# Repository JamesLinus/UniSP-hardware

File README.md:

# UniSP-hardware
(..sketch..)

## About UniSP

UniSP is an open source project that aims to develop universal high power SMPS (Swiched-mode power supply) platform.

Main features:
- based on full bridge DC/DC converter
- digital controll based on STM32F334 microcontroller
- modular desing
- communication interface
- output module interface

Source code and doc for software part of project can be find on <https://github.com/UniSP/UniSP-software>

## About UniSP-hardware

UniSP-hardware is dividing into the following modules:
- **UniSP-mainboard** - main power section including primary and secondary side of converter.
- **UniSP-pfc-LT1249** - active power factor correction based on Linear LT1249.
- **UniSP-pfc-bl** - (planned) bridgeless PFC with low power supply on board.
- **UniSP-driver** - main control unit with STM32F334R8 uC on board
- **UniSP-bridge_driver** - full bridge transistors driver.
- **UniSP-bridge_driver_PSFB** - (planned) full bridge transistors driver supporting phase shifted resonant PWM controll technique.
- **UniSP-rectifier_driver** - (planned) synchronous rectifier transistors driver (GDT?).
- Optionally output module (**UniSP-out_module**) controled by UniSP output interface.

Each module (except UniSP output modules) is placed in individual subfolder in UniSP-hardware repository. 

UniSP output modules (hardware and software) will be places in a separated repositories.

UniSP output interface consists of:
- 2 current sense input (fast speed and normal speed)
- 2 voltage sense input (fast speed and normal speed)
- 2 high-resolution timer outputs (TIMERD and TIMERE - each with 2 channel)
- 15V supply output
  
### Details

| Module                  | Circuit diagram                                      | PCB status   | Next action         |
|-------------------------|------------------------------------------------------|--------------|---------------------|
| UniSP-mainboard         | [Link](doc/scheme/UniSP-mainboard.pdf)               | In progress  |                     |
| UniSP-pfc-LT1249        | [Link](doc/scheme/UniSP-pfc-LT1249.pdf)              | In progress  | Add aux PS section  |
| UniSP-pfc-bl            | In progress                                          | ----         |                     |
| UniSP-driver            | [Link](doc/scheme/UniSP-driver.pdf)                  | In progress  |                     |
| UniSP-bridge_driver     | [Link](doc/scheme/UniSP-bridge_driver.pdf)           | Done         |                     |
| UniSP-bridge_driver_PSFB| [Link](doc/scheme/UniSP-bridge_driver_PSFB.pdf)      | In progress  |                     |
| UniSP-rectifier_driver  | In progress                                          | ----         |                     |

Please visit the author's website ~~www.railab.me~~ (under construction) for worklogs, articles and other interesting content ;]

### TODO
- finish new mainboard PCB
- add 3D models
- add modules to official KiCad library
- 3D model (in FreeCAD)
- chassis
- EMI/RFI shielding ?
- improve EMC

### UniSP-hardware roadmap
- documentation
- costs optimisation
- user interface
- synchronous rectification on secondary side
- soft swiching on primary side (phase shifted full bridge)
- bridgeless PFC

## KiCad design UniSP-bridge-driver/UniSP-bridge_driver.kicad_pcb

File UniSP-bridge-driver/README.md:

#UniSP-bridge_driver-v.0.2

### Basic spec

### TODO in next revision
- SMT transformers?
- some testing pads?

### History
v0.1:

- Initial revision.

v0.2:

- Fixed some bug.
- Github init.

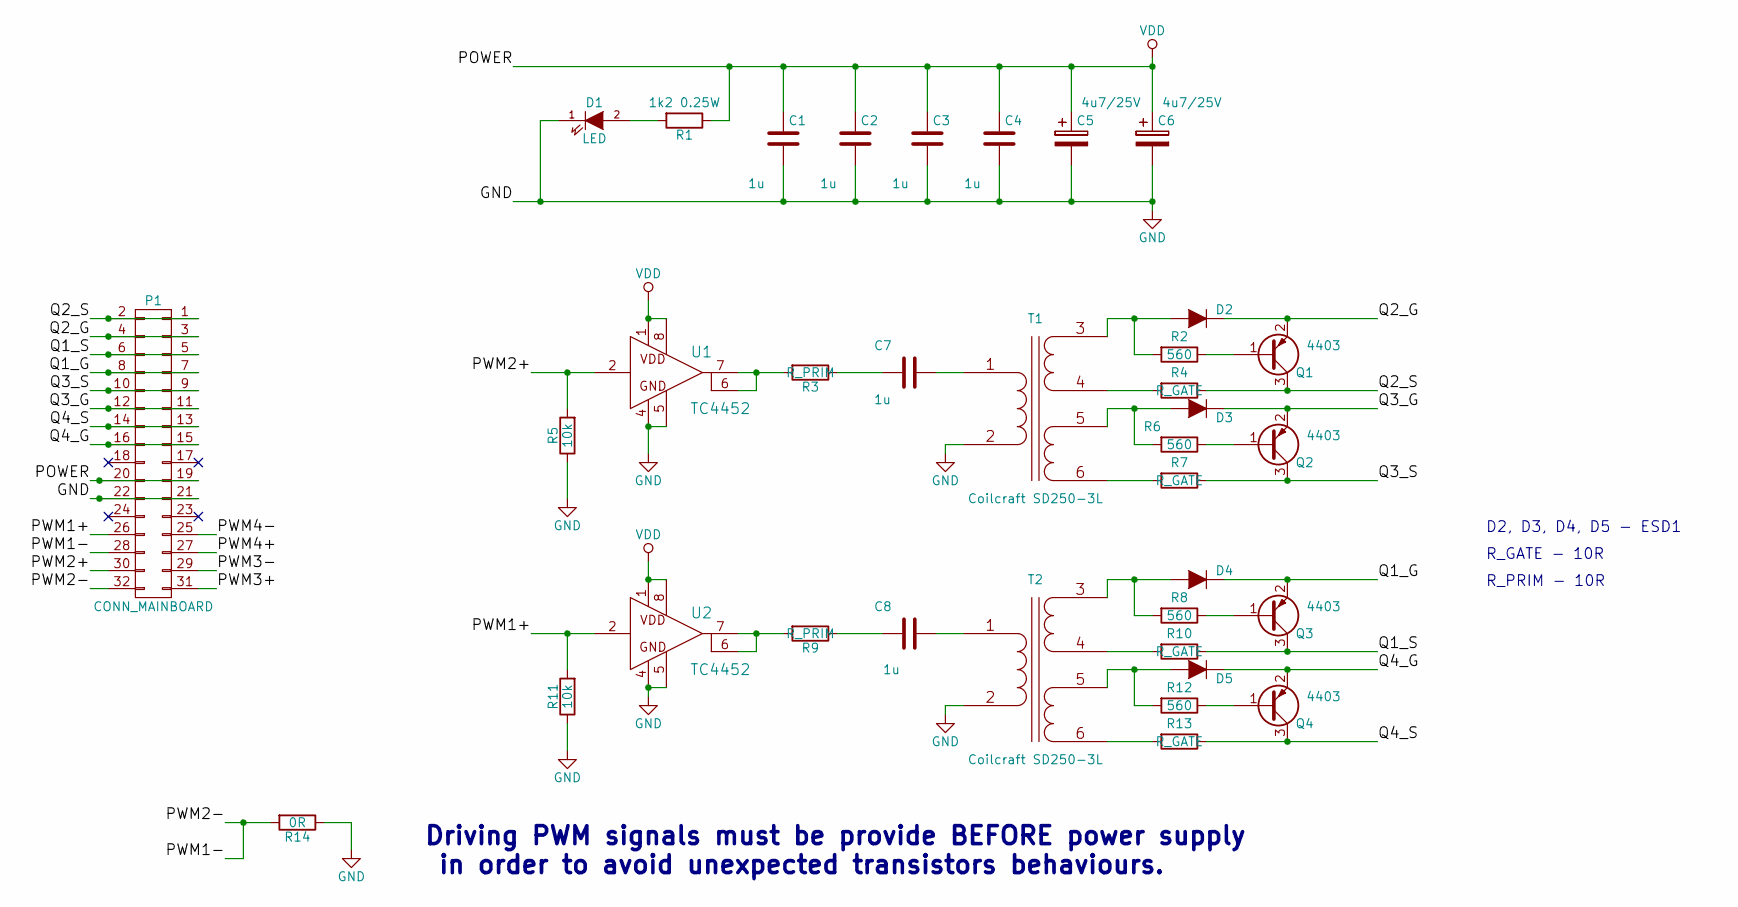
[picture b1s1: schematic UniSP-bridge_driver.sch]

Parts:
C1, C2, C3, C4, C7, C8: 1u; C_1206_HandSoldering
C5, C6: 4u7/25V; TantalC_SizeB_EIA-3528_HandSoldering
D1: LED; LED-0603
D2, D3, D4, D5: ESD1; SMA_Handsoldering
P1: CONN_MAINBOARD; Pin_Header_Angled_2x16
Q1, Q2, Q3, Q4: 4403; SOT-23_Handsoldering
R1: 1k2 0.25W; R_1206_HandSoldering
R2, R6, R8, R12: 560; R_1206_HandSoldering
R3, R9: R_PRIM; R_1206_HandSoldering
R4, R7, R10, R13: R_GATE; R_1206_HandSoldering
R5, R11: 10k; R_0805_HandSoldering
R14: 0R; R_0805_HandSoldering
T1, T2: Coilcraft SD250-3L; Coilcraft-SD250-3L
U1, U2: TC4452; SOIC-8_3.9x4.9mm_Pitch1.27mm

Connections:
/PWM1+: P1.26, R11.2, U2.2
/PWM1-: P1.28, P1.32, R14.2
/PWM2+: P1.30, R5.2, U1.2
/PWM3+: P1.31
/PWM3-: P1.29
/PWM4+: P1.27
/PWM4-: P1.25
/Q1_G: D4.1 (K), P1.7, P1.8, Q3.2 (E)
/Q1_S: P1.5, P1.6, Q3.3 (C), R10.1
/Q2_G: D2.1 (K), P1.3, P1.4, Q1.2 (E)
/Q2_S: P1.1, P1.2, Q1.3 (C), R4.1
/Q3_G: D3.1 (K), P1.11, P1.12, Q2.2 (E)
/Q3_S: P1.9, P1.10, Q2.3 (C), R7.1
/Q4_G: D5.1 (K), P1.15, P1.16, Q4.2 (E)
/Q4_S: P1.13, P1.14, Q4.3 (C), R13.1
GND: C1.2, C2.2, C3.2, C4.2, C5.2, C6.2, D1.1 (K), P1.21, P1.22, R5.1, R11.1, R14.1, T1.2 (AB), T2.2 (AB), U1.4, U1.5, U2.4, U2.5
unnamed: C7.1, T1.1 (AA)
unnamed: C7.2, R3.1
unnamed: C8.1, T2.1 (AA)
unnamed: C8.2, R9.1
unnamed: D1.2 (A), R1.2
unnamed: D2.2 (A), R2.2, T1.3 (SA)
unnamed: D3.2 (A), R6.2, T1.5 (SC)
unnamed: D4.2 (A), R8.2, T2.3 (SA)
unnamed: D5.2 (A), R12.2, T2.5 (SC)
unnamed: Q1.1 (B), R2.1
unnamed: Q2.1 (B), R6.1
unnamed: Q3.1 (B), R8.1
unnamed: Q4.1 (B), R12.1
unnamed: R3.2, U1.6, U1.7
unnamed: R4.2, T1.4 (SB)
unnamed: R7.2, T1.6 (SD)
unnamed: R9.2, U2.6, U2.7
unnamed: R10.2, T2.4 (SB)
unnamed: R13.2, T2.6 (SD)
VDD: C1.1, C2.1, C3.1, C4.1, C5.1, C6.1, P1.19, P1.20, R1.1, U1.1, U1.8, U2.1, U2.8

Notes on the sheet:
D2, D3, D4, D5 - ESD1
Driving PWM signals must be provide BEFORE power supply in order to avoid unexpected transistors behaviours.
R_GATE - 10R
R_PRIM - 10R

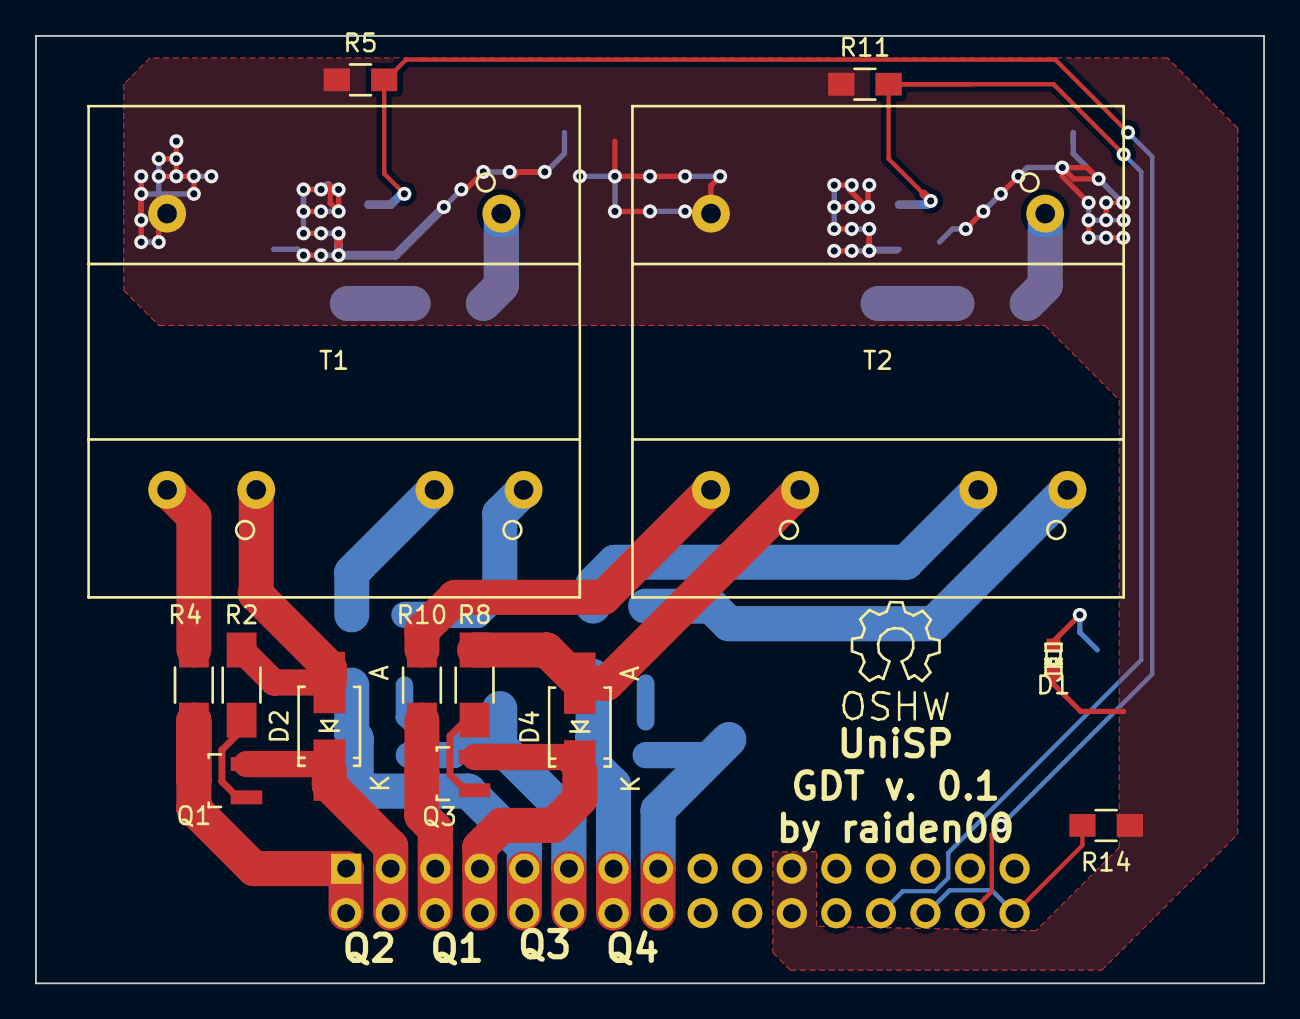
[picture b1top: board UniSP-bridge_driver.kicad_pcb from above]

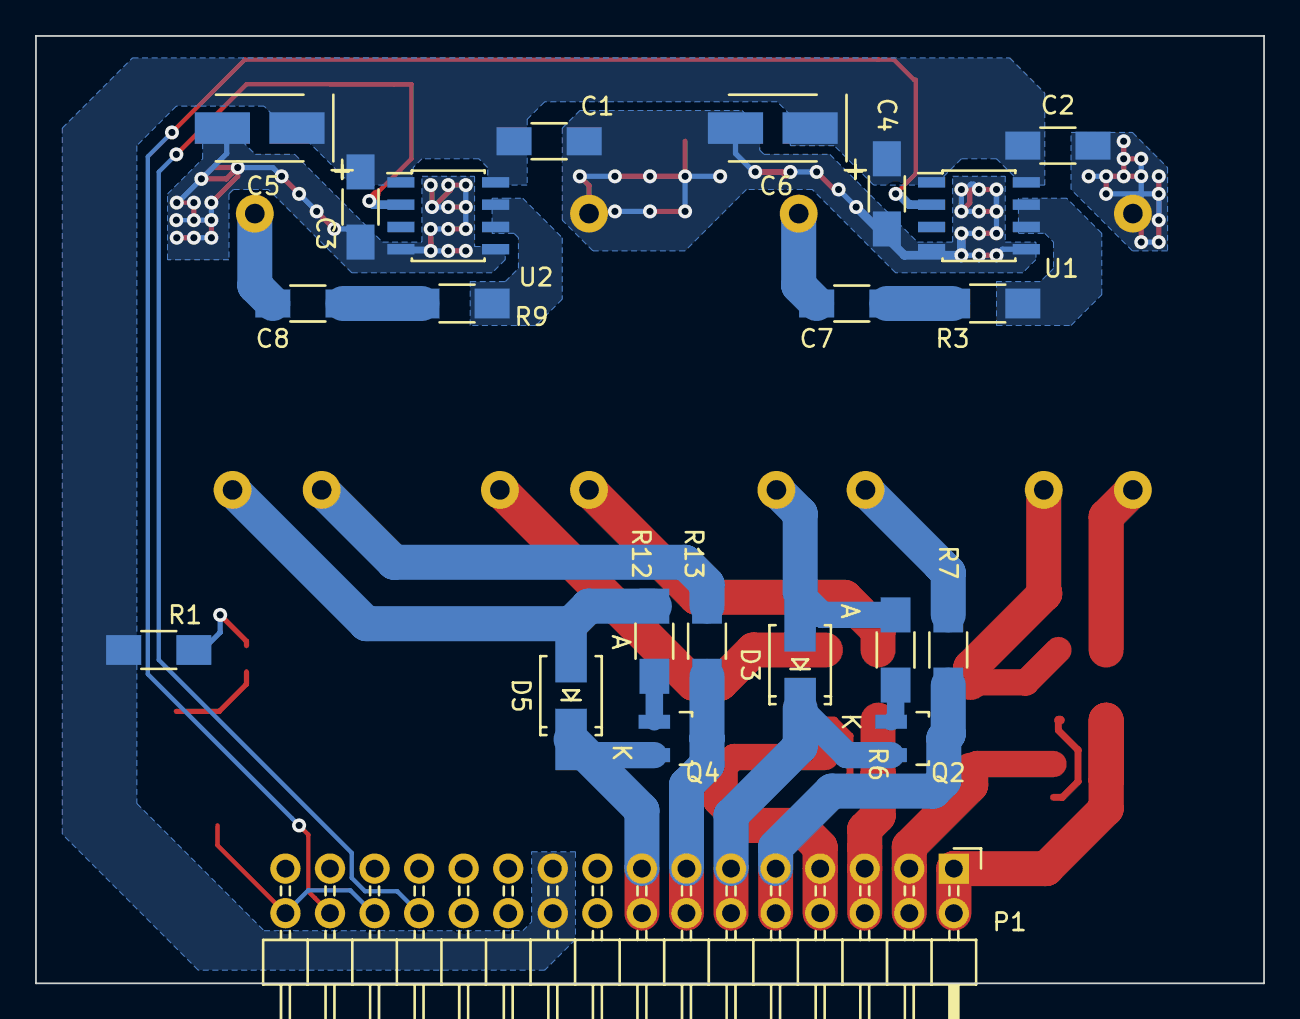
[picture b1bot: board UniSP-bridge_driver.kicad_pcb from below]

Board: 2 copper layers, 70.0 x 54.0 mm, 36 parts (22 on the bottom side), 32 nets.

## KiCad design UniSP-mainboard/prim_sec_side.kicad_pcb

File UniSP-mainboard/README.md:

# UniSP-mainboard-v.0.2

### Basic spec

### TODO
- finish PCB
- test points?

### History
v0.1:

- Initial revision.

v0.2:

- Fixed some bug.
- Added optional inductance in series with transformer.
- CT now ahed of transistors bridge.
- Github init.

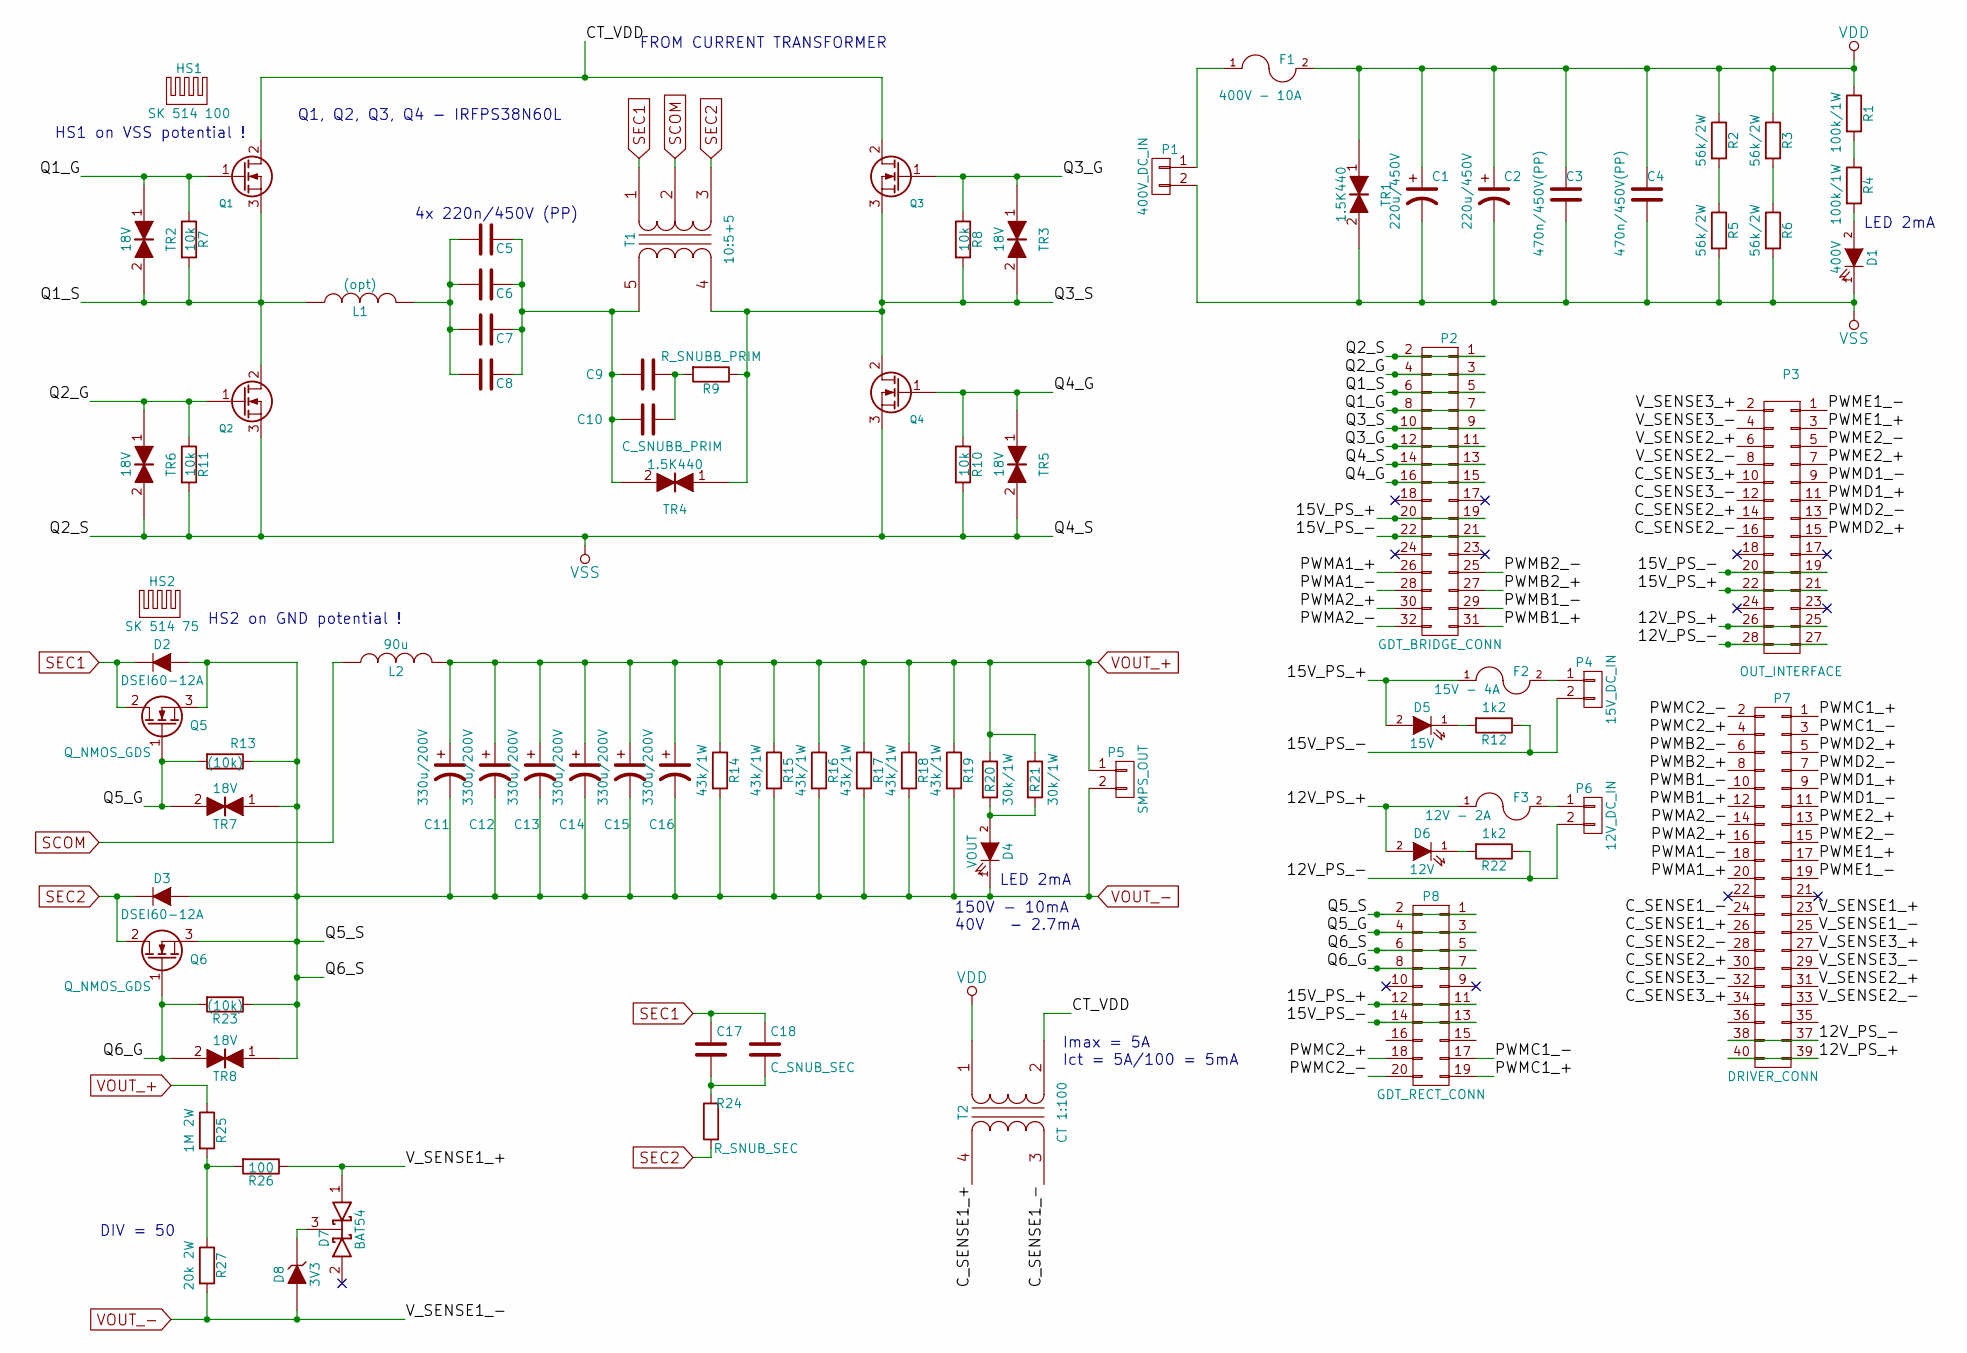
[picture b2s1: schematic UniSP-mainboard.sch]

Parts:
C1, C2: 220u/450V; C_Radial_D30_L51_P10
C3, C4: 470n/450V(PP); C_Rect_L32_W15_P27
C5, C6, C7, C8: 220n/450V (PP); C_Rect_L18_W9_H15_P15
C9, C10: C_SNUBB_PRIM; C_Rect_L7_W6_P5
C11, C12, C13, C14, C15, C16: 330u/200V; C_Radial_D22_L41_P10
C17, C18: C_SNUB_SEC; C_Rect_L7_W6_P5
D1: 400V; LED-3MM
D2, D3: DSEI60-12A; Diode_TO-247_Vertical
D4: VOUT; LED-3MM
D5: 15V; LED-0603
D6: 12V; LED-0603
D7: BAT54; SOT-23_Handsoldering
D8: 3V3; MiniMELF_Handsoldering
F1: 400V - 10A; FUSE_3
F2: 15V - 4A; Smps-fuse-154
F3: 12V - 2A; Smps-fuse-154
HS1: SK 514 100; Heatsink-SK-514-100
HS2: SK 514 75; Heatsink-SK-514-75
L1: (opt); Inductor-DTMSS40-0.1-20
L2: 90u; Inductor-DTMSS40-0.1-20
P1: 400V_DC_IN; CONN_2_20A
P2: GDT_BRIDGE_CONN; Socket_Strip_Straight_2x16
P3: OUT_INTERFACE; Socket_Strip_Straight_2x14
P4: 15V_DC_IN; bornier2
P5: SMPS_OUT; CONN_2_20A
P6: 12V_DC_IN; bornier2
P7: DRIVER_CONN; Socket_Strip_Straight_2x20
P8: GDT_RECT_CONN; Socket_Strip_Straight_2x10
Q1, Q2, Q3, Q4: IRFPS38N60L; TO-247_Vertical_Neutral123_largePads
Q5, Q6: Q_NMOS_GDS; TO-247_Vertical_Neutral123_largePads
R1, R4: 100k/1W; R_2512_HandSoldering
R2, R3, R5, R6: 56k/2W; R_2512_HandSoldering
R7, R8, R10, R11: 10k; R_2512_HandSoldering
R9: R_SNUBB_PRIM; Resistor_Vertical_RM7.5mm
R12, R22: 1k2; R_1206_HandSoldering
R13, R23: (10k); R_2512_HandSoldering
R14, R15, R16, R17, R18, R19: 43k/1W; R_2512_HandSoldering
R20, R21: 30k/1W; R_2512_HandSoldering
R24: R_SNUB_SEC; Resistor_Vertical_RM7.5mm
R25: 1M 2W; Resistor_Horizontal_RM15mm
R26: 100; R_1206_HandSoldering
R27: 20k 2W; Resistor_Horizontal_RM15mm
T1: 10:5+5; TRAFO2_E71_H
T2: CT 1:100; Coilcraft-CS1xxx
TR1, TR4: 1.5K440; Diode-DO-214AB_Handsoldering
TR2, TR3, TR6, TR7, TR8: 18V; SMB_Handsoldering
TR5: 18V; SMB_Standard

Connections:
/12V_PS_+: D6.2 (A), F3.1, P3.25, P3.26, P7.39, P7.40
/12V_PS_-: P3.27, P3.28, P6.2, P7.37, P7.38, R22.1
/15V_PS_+: D5.2 (A), F2.1, P2.19, P2.20, P3.21, P3.22, P8.11, P8.12
/15V_PS_-: P2.21, P2.22, P3.19, P3.20, P4.2, P8.13, P8.14, R12.1
/CT_VDD: Q1.2 (D), Q3.2 (D), T2.2 (AB)
/C_SENSE1_+: P7.26, T2.4 (SB)
/C_SENSE1_-: P7.24, T2.3 (SA)
/C_SENSE2_+: P3.14, P7.30
/C_SENSE2_-: P3.16, P7.28
/C_SENSE3_+: P3.10, P7.34
/C_SENSE3_-: P3.12, P7.32
/PWMA1_+: P2.26, P7.20
/PWMA1_-: P2.28, P7.18
/PWMA2_+: P2.30, P7.16
/PWMA2_-: P2.32, P7.14
/PWMB1_+: P2.31, P7.12
/PWMB1_-: P2.29, P7.10
/PWMB2_+: P2.27, P7.8
/PWMB2_-: P2.25, P7.6
/PWMC1_+: P7.1, P8.19
/PWMC1_-: P7.3, P8.17
/PWMC2_+: P7.4, P8.18
/PWMC2_-: P7.2, P8.20
/PWMD1_+: P3.11, P7.9
/PWMD1_-: P3.9, P7.11
/PWMD2_+: P3.15, P7.5
/PWMD2_-: P3.13, P7.7
/PWME1_+: P3.3, P7.17
/PWME1_-: P3.1, P7.19
/PWME2_+: P3.7, P7.13
/PWME2_-: P3.5, P7.15
/Q1_G: P2.7, P2.8, Q1.1 (G), R7.1, TR2.1
/Q1_S: L1.1, P2.5, P2.6, Q1.3 (S), Q2.2 (D), R7.2, TR2.2
/Q2_G: P2.3, P2.4, Q2.1 (G), R11.1, TR6.1
/Q3_G: P2.11, P2.12, Q3.1 (G), R8.1, TR3.1
/Q3_S: P2.9, P2.10, Q3.3 (S), Q4.2 (D), R8.2, R9.1, T1.4 (S1), TR3.2, TR4.1
/Q4_G: P2.15, P2.16, Q4.1 (G), R10.1, TR5.1
/Q5_G: P8.3, P8.4, Q5.1 (G), R13.2, TR7.2
/Q6_G: P8.7, P8.8, Q6.1 (G), R23.2, TR8.2
/V_SENSE1_+: D7.1 (A), P7.23, R26.1
/V_SENSE2_+: P3.6, P7.31
/V_SENSE2_-: P3.8, P7.33
/V_SENSE3_+: P3.2, P7.27
/V_SENSE3_-: P3.4, P7.29
unnamed: C5.2, C6.2, C7.2, C8.2, L1.2
unnamed: C9.1, C10.1, R9.2
unnamed: C5.1, C6.1, C7.1, C8.1, C9.2, C10.2, T1.5 (S2), TR4.2
unnamed: C17.2, C18.2, R24.2
unnamed: D1.2 (A), R4.2
unnamed: D4.2 (A), R20.2, R21.2
unnamed: D5.1 (K), R12.2
unnamed: D6.1 (K), R22.2
unnamed: D7.3 (K), D8.1 (K)
unnamed: F1.1, P1.1
unnamed: F2.2, P4.1
unnamed: F3.2, P6.1
unnamed: R1.2, R4.1
unnamed: R2.2, R5.1
unnamed: R3.2, R6.1
unnamed: R25.2, R26.2, R27.1
SCOM: L2.1, T1.2 (PM)
SEC1: C17.1, C18.1, D2.1 (K), Q5.2 (D), T1.1 (PR1)
SEC2: D3.1 (K), Q6.2 (D), R24.1, T1.3 (PR2)
VDD: C1.1, C2.1, C3.2, C4.2, F1.2, R1.1, R2.1, R3.1, T2.1 (AA), TR1.1
VOUT_+: C11.1, C12.1, C13.1, C14.1, C15.1, C16.1, L2.2, P5.1, R14.1, R15.1, R16.1, R17.1, R18.1, R19.1, R20.1, R21.1, R25.1
VOUT_-: C11.2, C12.2, C13.2, C14.2, C15.2, C16.2, D2.2 (A), D3.2 (A), D4.1 (K), D8.2 (A), HS2.1, HS2.2, P5.2, P7.25, P8.1, P8.2, P8.5, P8.6, Q5.3 (S), Q6.3 (S), R13.1, R14.2, R15.2, R16.2, R17.2, R18.2, R19.2, R23.1, R27.2, TR7.1, TR8.1
VSS: C1.2, C2.2, C3.1, C4.1, D1.1 (K), HS1.1, HS1.2, HS1.3, P1.2, P2.1, P2.2, P2.13, P2.14, Q2.3 (S), Q4.3 (S), R5.2, R6.2, R10.2, R11.2, TR1.2, TR5.2, TR6.2

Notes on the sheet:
DIV = 50
Imax = 5A Ict = 5A/100 = 5mA
150V - 10mA 40V - 2.7mA
LED 2mA
4x 220n/450V (PP)
Q1, Q2, Q3, Q4 - IRFPS38N60L
FROM CURRENT TRANSFORMER
HS1 on VSS potential !
HS2 on GND potential !

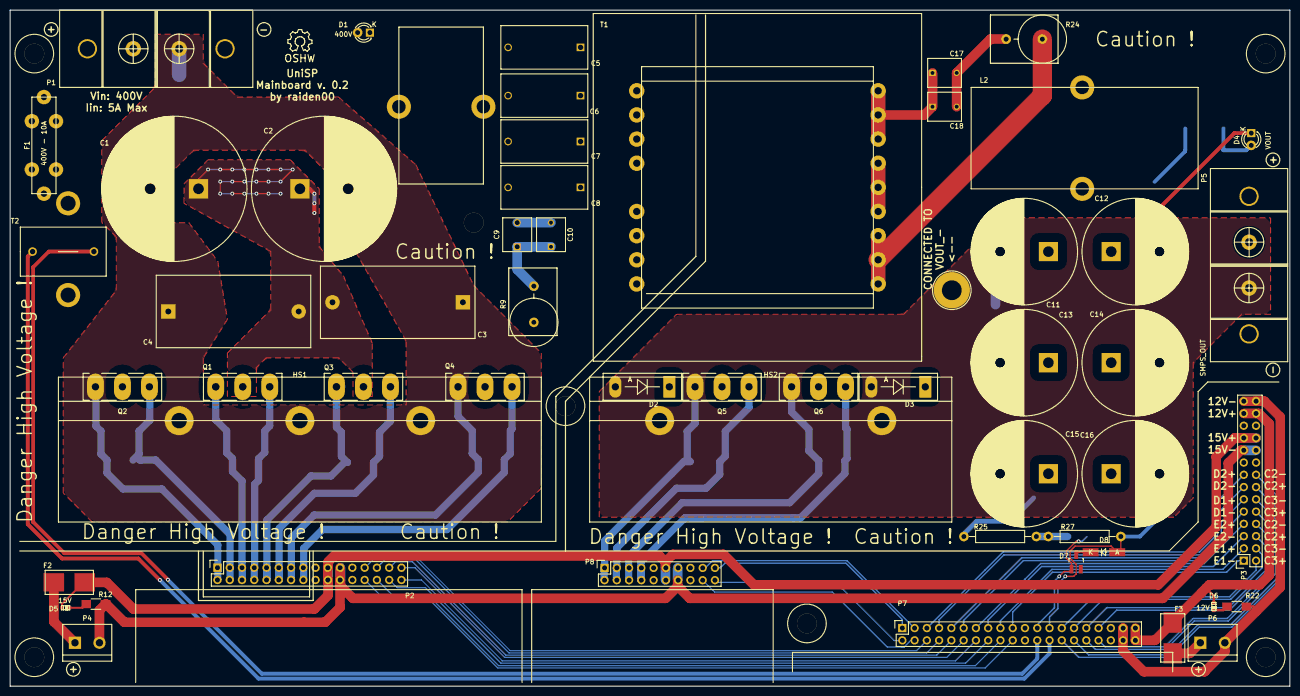
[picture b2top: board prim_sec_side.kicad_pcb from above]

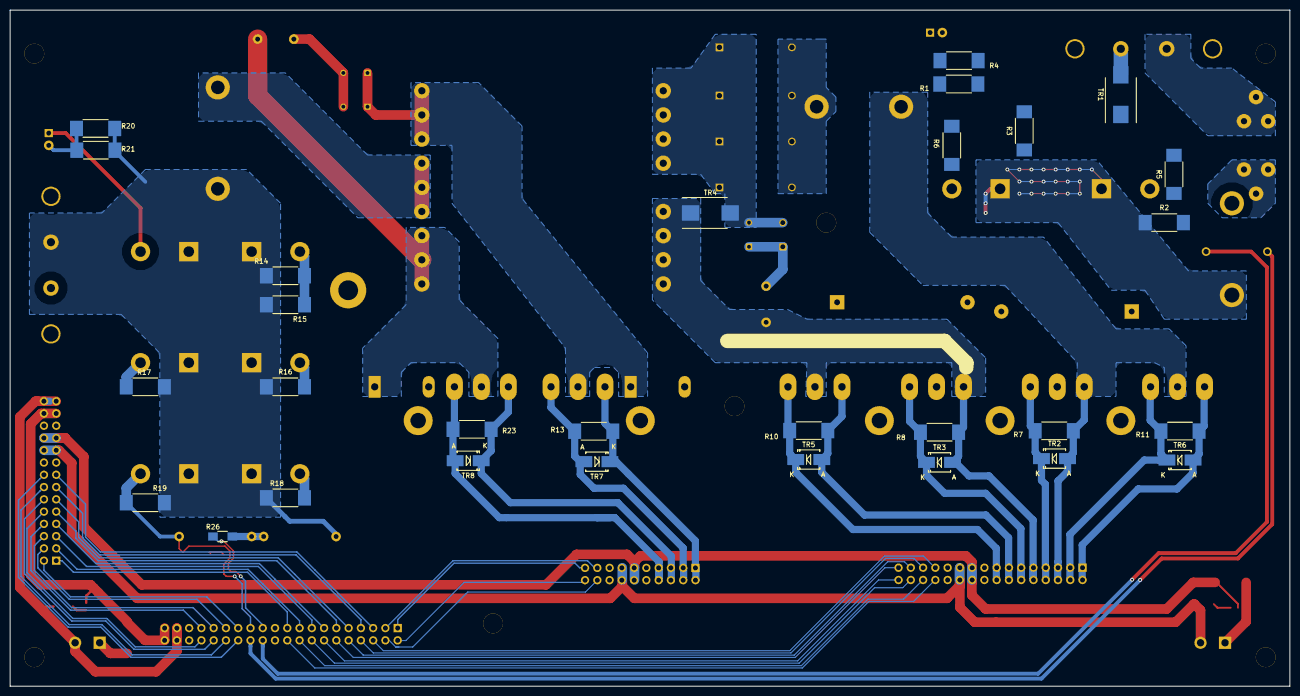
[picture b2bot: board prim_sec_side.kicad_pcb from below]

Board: 2 copper layers, 265.0 x 140.0 mm, 84 parts (29 on the bottom side), 67 nets.

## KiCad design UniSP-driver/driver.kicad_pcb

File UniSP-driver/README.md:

#UniSP-driver-v.0.2

### Basic spec

### TODO
- finish new driver PCB
- add test points
- improve analog section
- some protection mechanism ?
- isolated communiaction iterface ?

### History
v0.1:

- Initial revision.

v0.2:

- Fixed some bug.
- Github init.

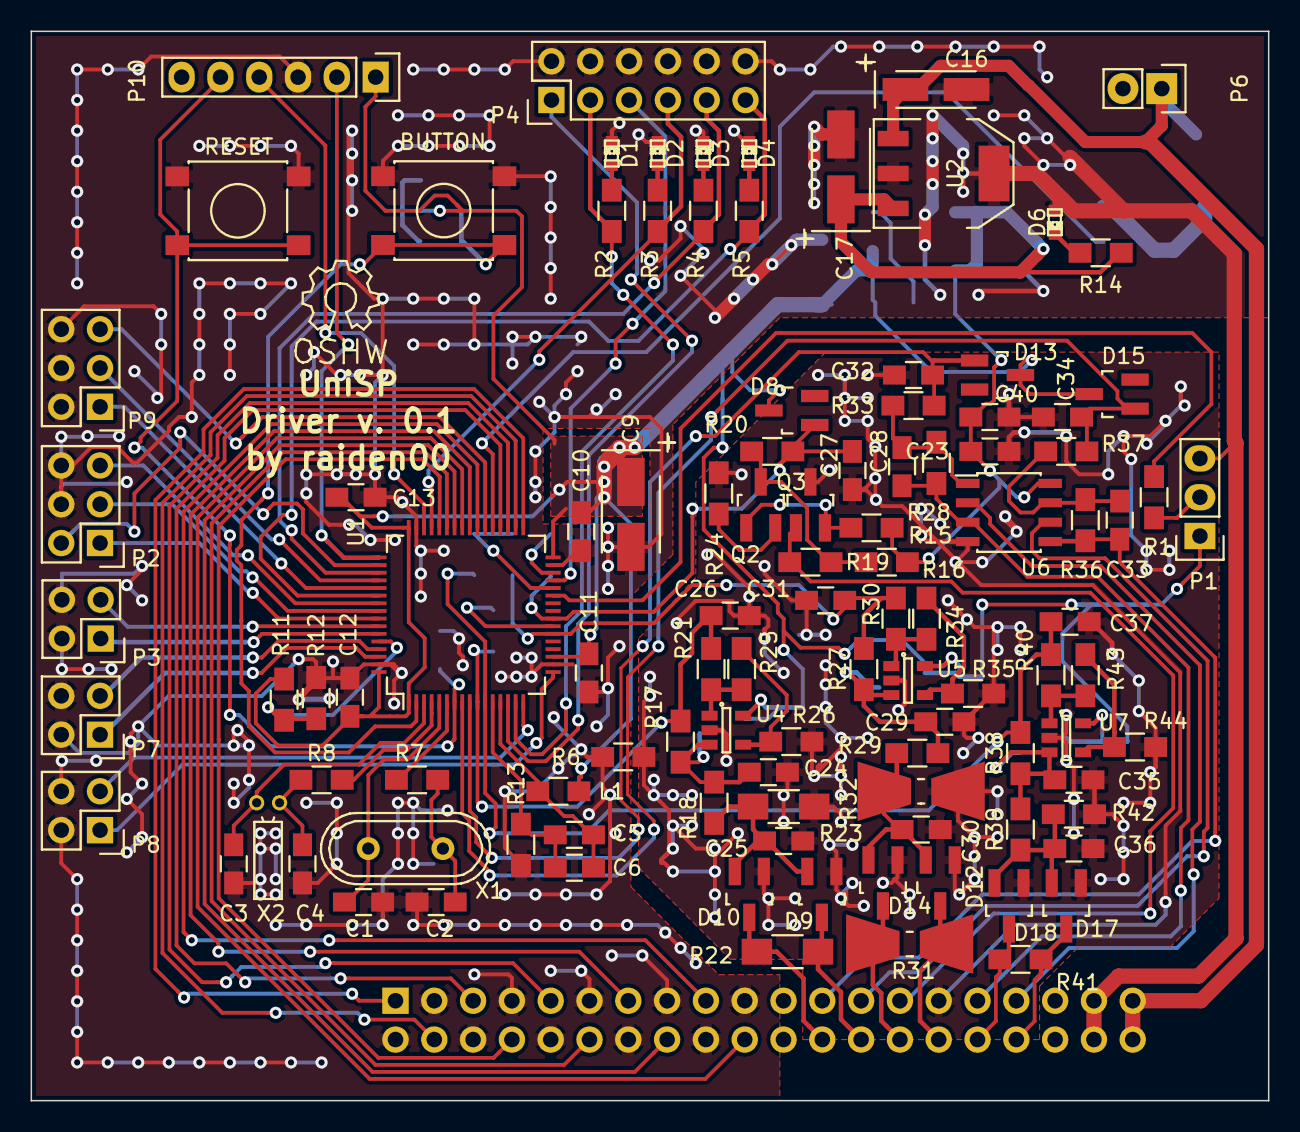
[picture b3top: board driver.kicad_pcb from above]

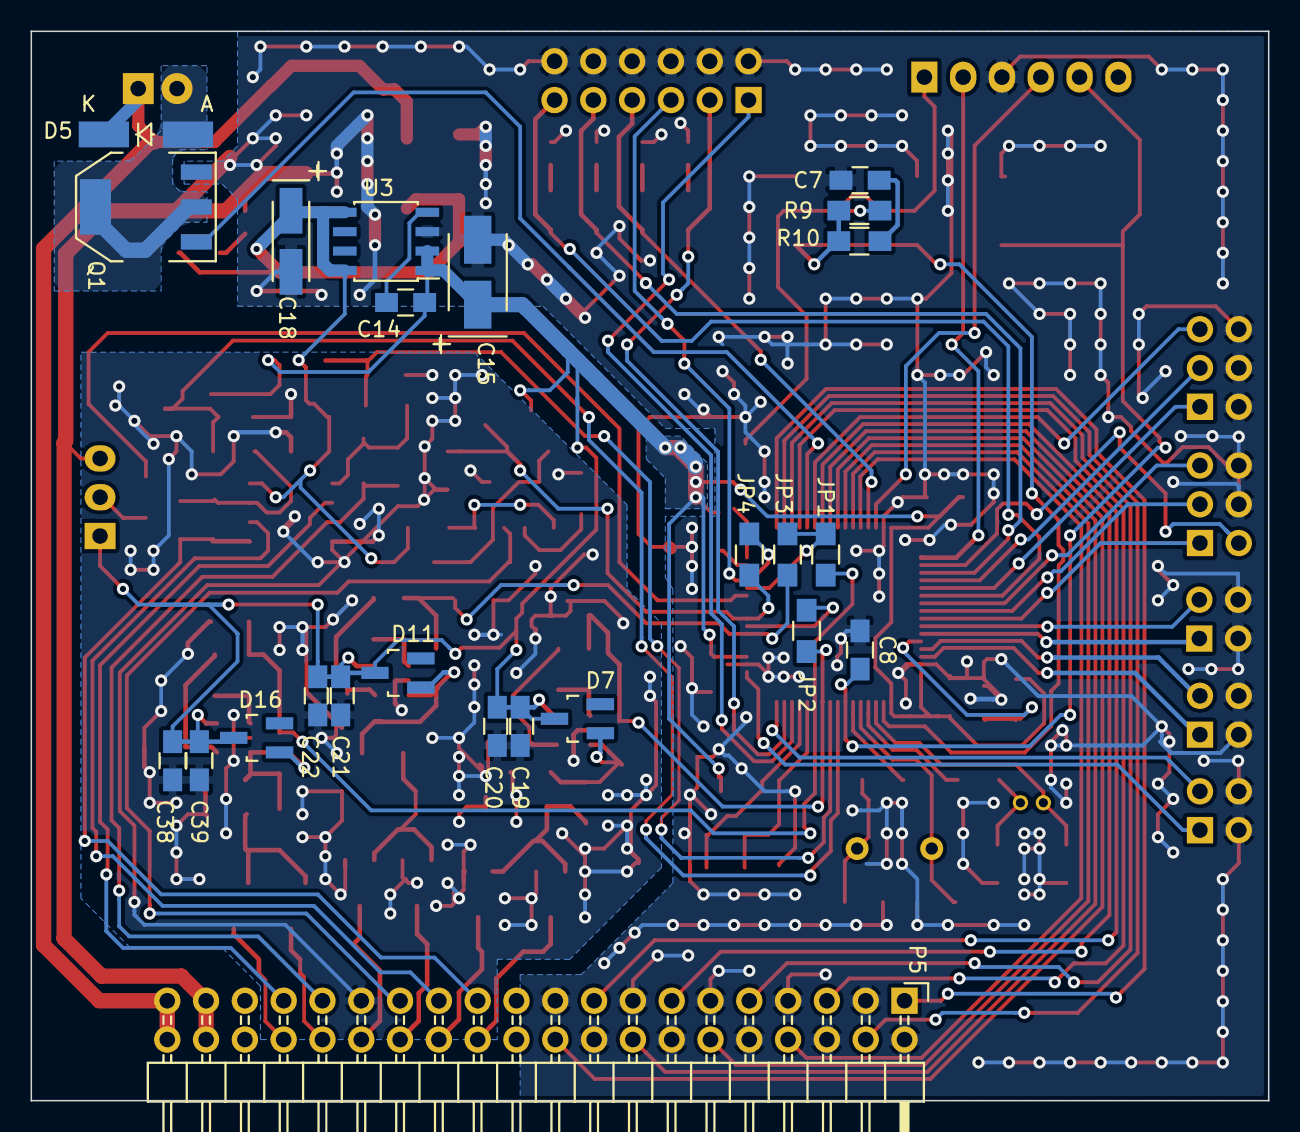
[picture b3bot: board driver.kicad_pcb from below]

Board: 2 copper layers, 81.0 x 70.0 mm, 131 parts (24 on the bottom side), 95 nets.

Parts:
C1, C2: 20p; C_0805_HandSoldering
C3, C4: 10p; C_0805_HandSoldering
C5, C14, C23: 10n; C_0805_HandSoldering
C6, C19, C21, C38, C40: 1u; C_0805_HandSoldering
C7, C8, C10, C11, C12, C13, C20, C22, C39: 100n; C_0805_HandSoldering
C9: 4u7; TantalC_SizeB_EIA-3528_HandSoldering
C15, C17: 10u; TantalC_SizeB_EIA-3528_HandSoldering
C16, C18: 3.3u; TantalC_SizeA_EIA-3216_HandSoldering
C24, C26, C29, C31, C32, C34, C37: 15n; C_0805_HandSoldering
C25, C30, C36: N/A; C_0805_HandSoldering
C27, C28, C33, C35: C; C_0805_HandSoldering
D1: MISC1; LED-0603
D2: MISC5; LED-0603
D3: MISC6; LED-0603
D4: MISC7; LED-0603
D5: 1N4148; Diode-MiniMELF_Handsoldering
D6: LED_5V; LED-0603
D7, D8, D11, D13, D15, D16: BAT54; SOT-23_Diode_Handsoldering
D9, D10, D12, D14, D17, D18: BAT54S; SOT-23_Handsoldering
JP1, JP2, JP3, JP4: Jumper_NC_Small; R_0805_HandSoldering
L1: BEAD; R_0805_HandSoldering
P1: ADC_TEMP; Pin_Header_Straight_1x03
P2: SPI; Pin_Header_Straight_2x03
P3: PFC_USART; Pin_Header_Straight_2x02
P4: MISC; Pin_Header_Straight_2x06
P5: MAINBOARD_CONN; Pin_Header_Angled_2x20
P6: FAN; Pin_Header_Straight_1x02
P7: COM2; Pin_Header_Straight_2x02
P8: COM1; Pin_Header_Straight_2x02
P9: HRTIM; Pin_Header_Straight_2x03
P10: SWD; Pin_Header_Straight_1x06
Q1: STN4NF03L; SOT-223
Q2: 2n3904; SOT-23_Handsoldering
Q3: 2n3906; SOT-23_Handsoldering
R1, R6, R8, R12, R13: 0; R_0805_HandSoldering
R2, R3, R4, R5: (510); R_0805_HandSoldering
R7: 390; R_0805_HandSoldering
R9: 4k7; R_0805_HandSoldering
R10: 100; R_0805_HandSoldering
R11, R17, R27, R38, R41: N/A; R_0805_HandSoldering
R14: 1.5k; R_0805_HandSoldering
R15: 10k; R_0805_HandSoldering
R16: 470; R_0805_HandSoldering
R18, R20, R21, R24, R28, R29, R30, R33, R36, R37, R40: 10; R_0805_HandSoldering
R19: 68k; R_0805_HandSoldering
R22: N/A; R_1206_HandSoldering
R23: R; R_1206_HandSoldering
R25, R26, R34, R35, R39, R42, R43, R44: R; R_0805_HandSoldering
R31: N/A; Resistor_SMDuniversal_0805to2512_HandSoldering
R32: R; Resistor_SMDuniversal_0805to2512_HandSoldering
SW1: BUTTON; SW_SPST_PTS645
SW2: RESET; SW_SPST_PTS645
U1: STM32F334Rx; LQFP-64_10x10mm_Pitch0.5mm
U2: LT1129CST-5; SOT-223
U3: LT1763-S8; SOIC-8_3.9x4.9mm_Pitch1.27mm
U4, U5, U7: MAX4130-SOT23; SOT-23-5
U6: LM358; SOIC-8_3.9x4.9mm_Pitch1.27mm
X1: 8MHz; Crystal_HC49-U_Vertical
X2: 32k; Crystal_Round_Horizontal_2mm

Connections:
+3.3VP: C9.1, C10.1, C11.1, C12.1, C13.1, C14.1, C15.1, C19.1, C20.1, C21.1, C22.1, C38.1, C39.1, D7.1, D8.1, D11.1, D13.1, D15.1, D16.1, L1.2, P1.1, P10.1, R9.1, R11.1, U1.1, U1.19, U1.32, U1.48, U1.64, U3.1, U3.2, U4.5, U5.5, U7.5
+5V: C17.1, C18.1, C23.1, C40.1, R14.1, R15.1, R16.1, U2.3, U3.5, U3.8, U6.8
+12C: C16.1, D5.1, P5.39, P5.40, P6.1, U2.1
/analog/ADC_CURR1: C26.1, JP2.2, R17.1, R21.2, U1.10
/analog/ADC_CURR2: C31.1, JP4.1, R27.1, R30.2, U1.22
/analog/ADC_CURR3: C37.1, JP1.2, R38.1, R40.2, U1.11
/analog/C_SENSE1_+: D9.3, P5.26, R22.1
/analog/C_SENSE1_-: D10.3, P5.24, R22.2
/analog/C_SENSE2_+: D12.3, P5.30, R31.1
/analog/C_SENSE2_-: D14.3, P5.28, R31.2
/analog/C_SENSE3_+: D17.3, P5.34, R41.1
/analog/C_SENSE3_-: D18.3, P5.32, R41.2
/analog/V_SENSE1_+: C33.1, P5.23, R36.1, U6.5
/analog/V_SENSE1_-: P5.25, U6.6
/analog/V_SENSE2_+: C28.1, P5.31, R28.1, U6.3
/analog/V_SENSE2_-: P5.33, U6.2
/analog/V_SENSE3_+: P5.27, Q3.1, R19.1
/uc/ADC_TEMP: R1.2, U1.27
/uc/ADC_V1: C34.1, D15.2, R37.2, U1.8
/uc/ADC_V2: C32.1, D13.2, R33.2, U1.9
/uc/ADC_V3: C27.1, D8.2, JP3.2, R20.2, U1.24
/uc/BUTTON: R9.2, R10.2, SW1.1, U1.2
/uc/COMP2_INP: JP2.1, U1.23
/uc/COMP4_INM: JP1.1, JP4.2, U1.28
/uc/COMP6_INP: JP3.1, U1.30
/uc/HRTIM1_CHA1: P5.20, U1.41
/uc/HRTIM1_CHA2: P5.16, U1.42
/uc/HRTIM1_CHB1: P5.12, U1.43
/uc/HRTIM1_CHB2: P5.8, U1.44
/uc/HRTIM1_CHC1: P5.1, U1.33
/uc/HRTIM1_CHC2: P5.4, U1.34
/uc/HRTIM1_CHD1: P5.9, U1.35
/uc/HRTIM1_CHD2: P5.5, U1.36
/uc/HRTIM1_CHE1: P5.17, U1.39
/uc/HRTIM1_CHE2: P5.13, U1.40
/uc/HRTIM1_EEV1: P9.3, U1.52
/uc/HRTIM1_EEV2: P9.1, U1.53
/uc/HRTIM1_FLT5: P9.5, U1.38
/uc/MISC0: P4.1, U1.14
/uc/MISC1: P4.3, R2.1, U1.15
/uc/MISC2: P8.3, U1.16
/uc/MISC3: P8.1, U1.17
/uc/MISC4: P4.5, U1.29
/uc/MISC5: P4.7, R3.1, U1.45
/uc/MISC6: P4.9, R4.1, U1.51
/uc/MISC7: P4.11, R5.1, U1.54
/uc/MISC8: P7.3, U1.61
/uc/MISC9: P7.1, U1.62
/uc/NRST: C8.1, P10.5, SW2.1, U1.7
/uc/OSC32_IN: C3.1, U1.3, X2.2
/uc/OSC32_OUT: R8.1, U1.4
/uc/OSC_IN: C1.1, U1.5, X1.2
/uc/OSC_OUT: R7.1, U1.6
/uc/SPI_MISO: P2.3, U1.56
/uc/SPI_MOSI: P2.1, U1.57
/uc/SPI_NSS: P2.2, U1.50
/uc/SPI_SCK: P2.5, U1.55
/uc/SWDCLK: P10.2, U1.49
/uc/SWDIO: P10.4, U1.46
/uc/TIM3_CH1: Q1.1, U1.37
/uc/USART_RX: P3.1, U1.59
/uc/USART_TX: P3.3, U1.58
/uc/VDDA: C5.2, C6.1, L1.1, U1.13
/uc/VSSA: C5.1, C6.2, R13.2, U1.12
GND: C1.2, C2.2, C3.2, C4.2, C7.2, C8.2, C9.2, C10.2, C11.2, C12.2, C13.2, C15.2, C16.2, C17.2, C18.2, D1.1, D2.1, D3.1, D4.1, D6.2, P1.3, P2.4, P2.6, P3.2, P3.4, P4.2, P4.4, P4.6, P4.8, P4.10, P4.12, P5.2, P5.3, P5.6, P5.7, P5.10, P5.11, P5.14, P5.15, P5.18, P5.19, P5.37, P5.38, P7.2, P7.4, P8.2, P8.4, P9.2, P9.4, P9.6, P10.3, Q1.3, R6.2, R12.2, R13.1, SW1.2, SW2.2, U1.18, U1.31, U1.47, U1.63, U2.2, U2.4, U3.3
GNDA: C19.2, C20.2, C21.2, C22.2, C23.2, C24.2, C25.2, C26.2, C27.2, C29.2, C30.2, C31.2, C32.2, C34.2, C35.2, C36.2, C37.2, C38.2, C39.2, C40.2, D9.1, D10.1, D12.1, D14.1, D17.1, D18.1, P5.29, Q3.3, R6.1, R23.2, R24.2, R26.2, R32.2, R35.2, R42.2, R44.2, U4.2, U5.2, U6.4, U7.2
unnamed: C2.1, R7.2, X1.1
unnamed: C4.1, R8.2, X2.1
unnamed: C7.1, R10.1
unnamed: C14.2, U3.4
unnamed: C24.1, D7.2, R17.2, R18.2, U4.3
unnamed: C25.1, D9.2, D10.2, R18.1, R23.1
unnamed: C28.2, R28.2, R33.1, U6.1
unnamed: C29.1, D11.2, R27.2, R29.2, U5.3
unnamed: C30.1, D12.2, D14.2, R29.1, R32.1
unnamed: C33.2, R36.2, R37.1, U6.7
unnamed: C35.1, D16.2, R38.2, R39.2, U7.3
unnamed: C36.1, D17.2, D18.2, R39.1, R42.1
unnamed: D1.2, R2.2
unnamed: D2.2, R3.2
unnamed: D3.2, R4.2
unnamed: D4.2, R5.2
unnamed: D5.2, P6.2, Q1.2
unnamed: D6.1, R14.2
unnamed: P1.2, R1.1
unnamed: Q2.1, Q3.2, R15.2
unnamed: Q2.2, R24.1
unnamed: Q2.3, R16.2, R19.2, R20.1
unnamed: R11.2, R12.1, U1.60
unnamed: R21.1, R25.1, U4.1
unnamed: R25.2, R26.1, U4.4
unnamed: R30.1, R34.1, U5.1
unnamed: R34.2, R35.1, U5.4
unnamed: R40.1, R43.1, U7.1
unnamed: R43.2, R44.1, U7.4

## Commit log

2016-01-11 license
2016-01-11 add .gitignore
2016-01-11 ignore inclomplete PCBs
2016-01-11 ignore org files
2016-01-11 add UniSP-bridge-driver
2016-01-11 add UniSP-bridge-driver-PSFB
2016-01-11 add UniSP-driver
2016-01-11 add UniSP-pfc-LT1249
2016-01-11 add UniSP-enclosure
2016-01-11 add UniSP-pfc-bl
2016-01-11 add UniSP-rectifier-driver
2016-01-11 add UniSP-mainboard
2016-01-11 add doc
2016-01-11 add README.md
2016-01-11 add UniSP logo
2016-01-11 templorary ignore UniSP-enclosure
2016-01-11 ignore .wrl files
